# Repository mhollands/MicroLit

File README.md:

# MicroLit
Simple BBC Microbit based design for controlling lighting from LED strips.

Read more at my website:https://projects.matthollands.com/category/microlit/

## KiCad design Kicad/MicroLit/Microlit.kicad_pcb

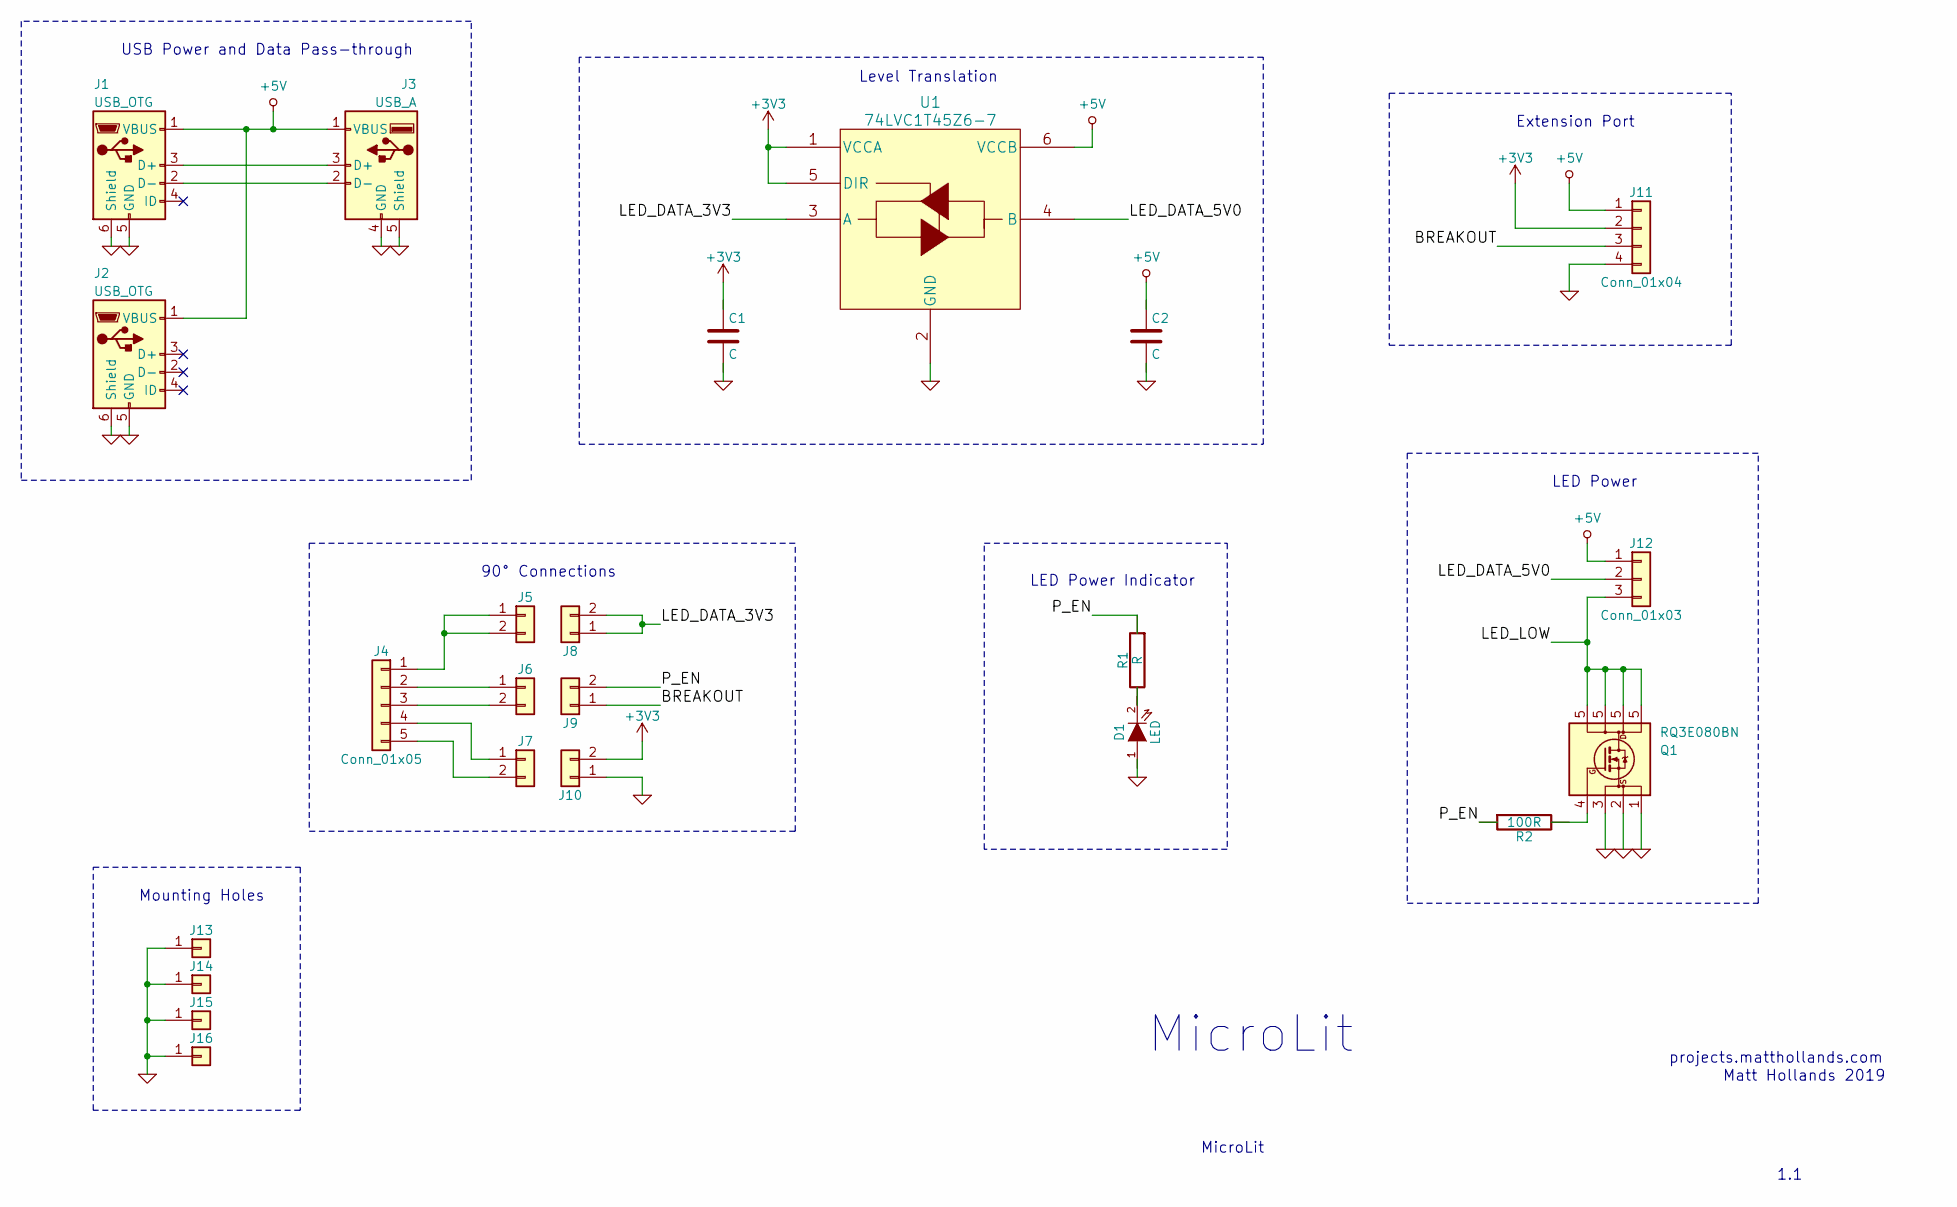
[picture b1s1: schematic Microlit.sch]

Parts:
C1, C2: C; C_0603
D1: LED; LED_0603
J1, J2: USB_OTG; USB_Micro-B
J3: USB_A; USB_A_Vertical
J4: Conn_01x05; MICROBIT_Bolt_On
J5, J6, J7: Conn_01x02; TSM-102-01-T-SH
J8, J9, J10: Conn_01x02; Pin_Header_Straight_1x02_Pitch2.54mm
J11: Conn_01x04; Pin_Header_Straight_1x04_Pitch2.54mm
J12: Conn_01x03; TerminalBlock_Phoenix_MPT-2.54mm_3pol
J13, J14, J15, J16: Conn_01x01; MountingHole_3.2mm_M3_Pad
Q1: RQ3E080BN; HSMT8
R1: R; R_0603
R2: 100R; R_0603
U1: 74LVC1T45Z6-7

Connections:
+3V3: C1.1, J10.2, J11.2, U1.1 (VCCA), U1.5 (DIR)
+5V: C2.1, J1.1 (VBUS), J2.1 (VBUS), J3.1 (VBUS), J11.1, J12.1, U1.6 (VCCB)
/BREAKOUT: J9.1, J11.3
/LED_DATA_3V3: J8.1, J8.2, U1.3 (A)
/LED_DATA_5V0: J12.2, U1.4 (B)
/LED_LOW: J12.3, Q1.5 (D)
/P_EN: J9.2, R1.1, R2.1
GND: C1.2, C2.2, D1.1 (A), J1.5 (GND), J1.6 (Shield), J2.5 (GND), J2.6 (Shield), J3.4 (GND), J3.5 (Shield), J10.1, J11.4, J13.1, J14.1, J15.1, J16.1, Q1.1 (S), Q1.2 (S), Q1.3 (S), U1.2 (GND)
unnamed: D1.2 (K), R1.2
unnamed: J1.2 (D-), J3.2 (D-)
unnamed: J1.3 (D+), J3.3 (D+)
unnamed: J4.1, J5.1, J5.2
unnamed: J4.2, J6.1
unnamed: J4.3, J6.2
unnamed: J4.4, J7.1
unnamed: J4.5, J7.2
unnamed: Q1.4 (G), R2.2

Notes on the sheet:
MicroLit
1.1
Matt Hollands 2019
projects.matthollands.com
USB Power and Data Pass-through
Level Translation
90° Connections
LED Power
Mounting Holes
Extension Port
LED Power Indicator

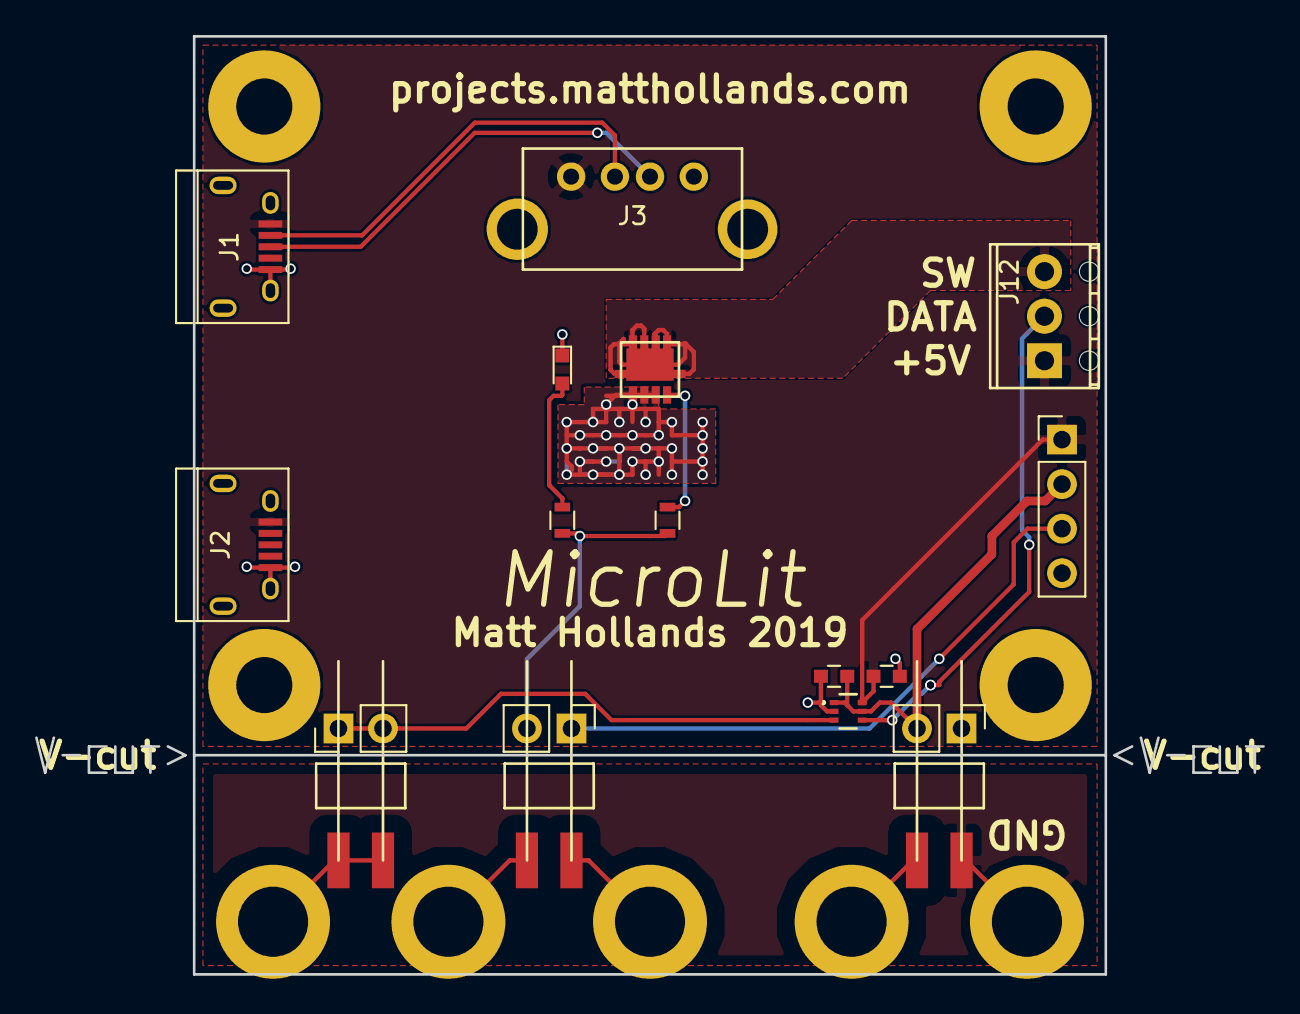
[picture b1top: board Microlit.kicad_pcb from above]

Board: 2 copper layers, 70.0 x 53.5 mm, 23 parts (1 on the bottom side), 17 nets.

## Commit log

2019-06-09 Added kicad files and micropython code
2019-09-22 update for v2
2019-09-22 added CAD for enclosure

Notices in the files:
parts and their libraries:
Copyright 2016 Accelerated Designs. All rights reserved.
